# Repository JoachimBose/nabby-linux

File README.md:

# Nabby linux
This contains the buildroot, uboot & linux configurations for a hobby project. To get started, clone a new buildroot repository outside this one.
Then, from within the buildroot repository, execute:
```bash
BR2_EXTERNAL=../nabby-linux make nabby-linux_defconfig
```
This will import all the files from this repository. If you are new to buildroot, consider taking a look around this repository to see what you just imported.

after you compiled your buildroot, you should get a `flash.bin` image as described in the genimage.cfg. To flash it, put the chip in FEL-mode.
This is done by shorting chipselect of the spiflash to 3.3 volts and powering on the device, after powerup remove the short. Now you can use:
```bash
sunxi-fel -p spiflash-write 0 flash.bin
```
to flash the board while its in FEL mode.

# VUCTF-2026 board

The VUCTF26 board has support for the w5500 dev boards like the w850io or the cheaper USR-ES1. There exist also the Spookystats vulnerable website and the portalctl privilege escalation 
challenge which can be compiled as a buildroot package. Any questions are welcome towards joa0405 on discord!

## Acknowledgements
When we built the nabby board, we forked the repository from: [BasicCode](https://github.com/BasicCode/F1C100-Business-Card/tree/main/board/f1c100-business-card)
and we are very thankful for their contribution & GPL-2.0 license. In BasicCodes repository, they acknowledged help from the following authors:

This project is based heavily on the work of others; I would like to acknowledge these project in particular:
* https://github.com/thirtythreeforty/businesscard-linux/tree/master
* https://github.com/florpor/licheepi-nano/tree/master
* [F1C100 Datasheet](https://whycan.com/files/members/3/F1C100s_Datasheet_V1_0.pdf)
* [Lichee-Pi Nano](https://wiki.sipeed.com/hardware/en/lichee/Nano/Nano.html)

*

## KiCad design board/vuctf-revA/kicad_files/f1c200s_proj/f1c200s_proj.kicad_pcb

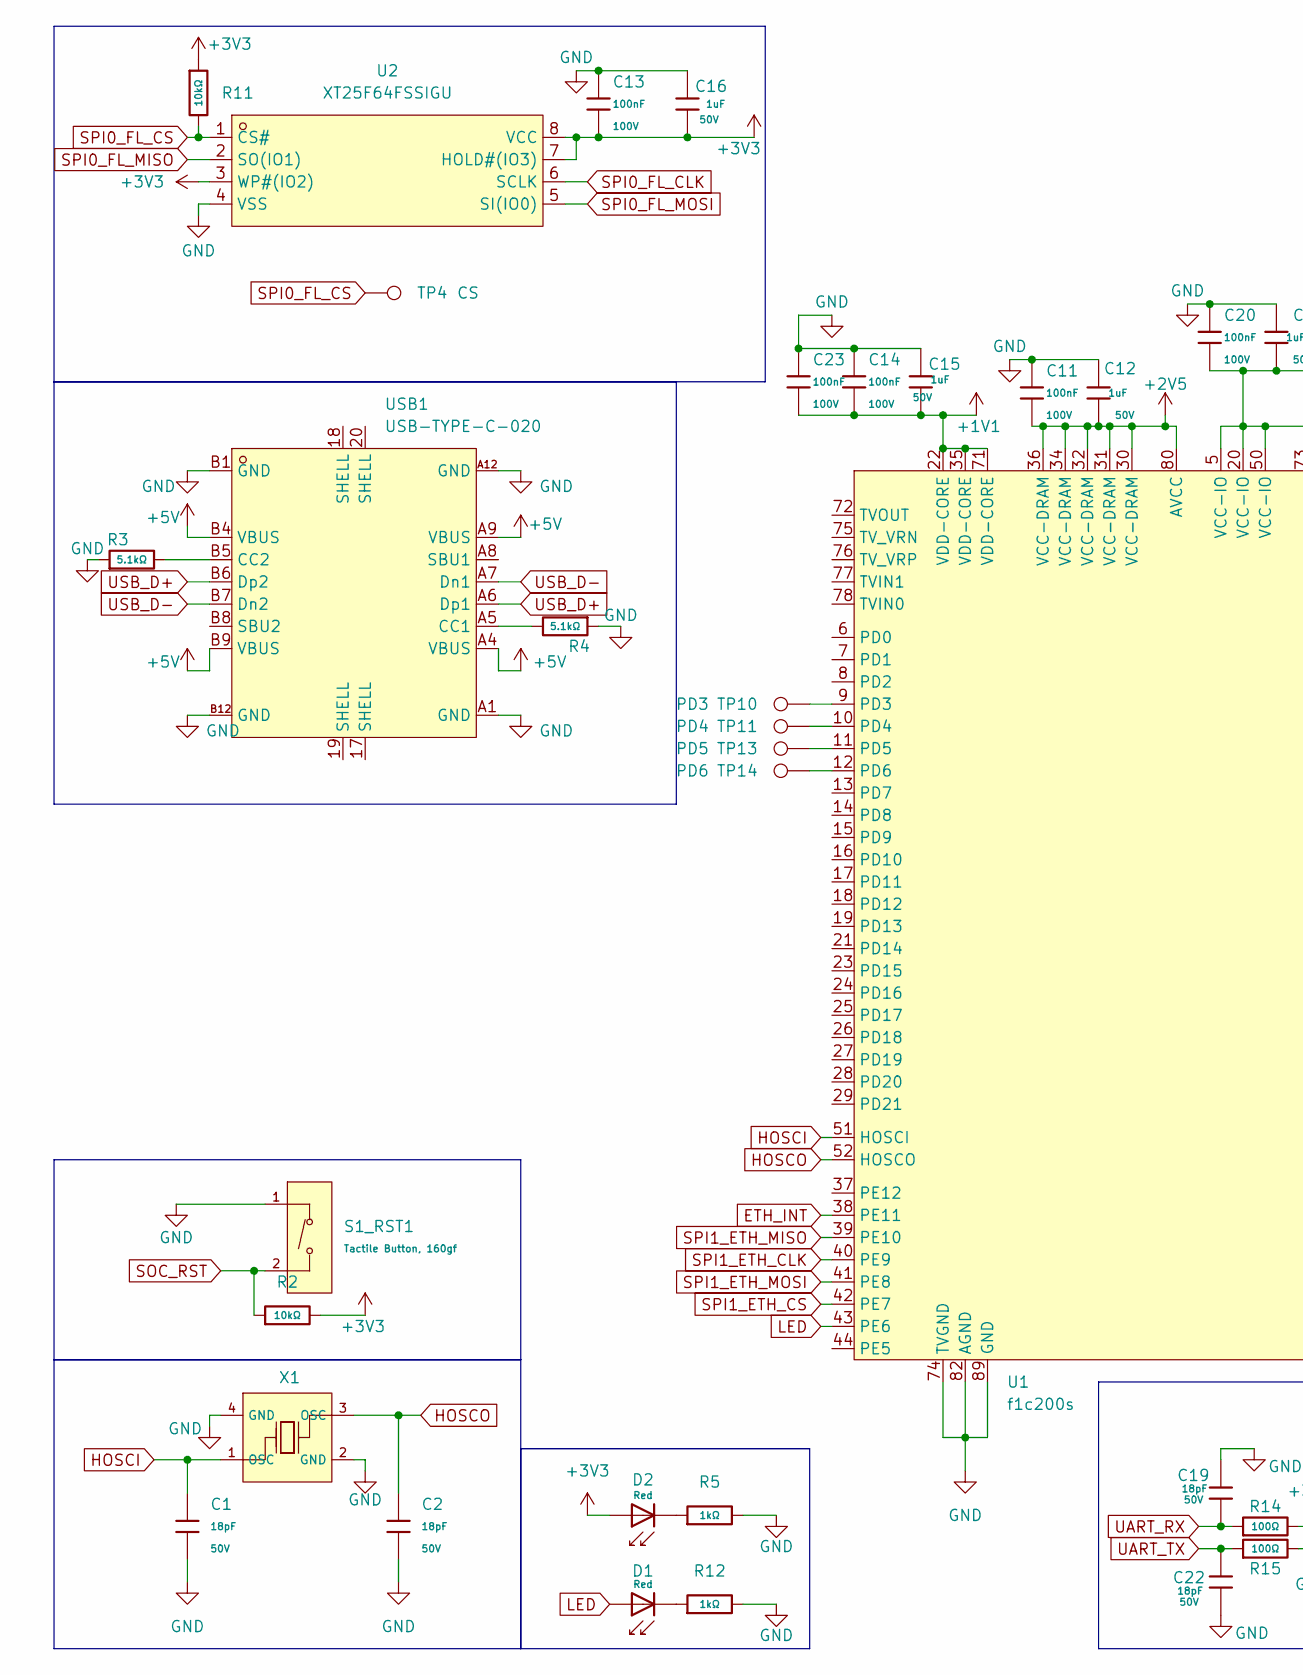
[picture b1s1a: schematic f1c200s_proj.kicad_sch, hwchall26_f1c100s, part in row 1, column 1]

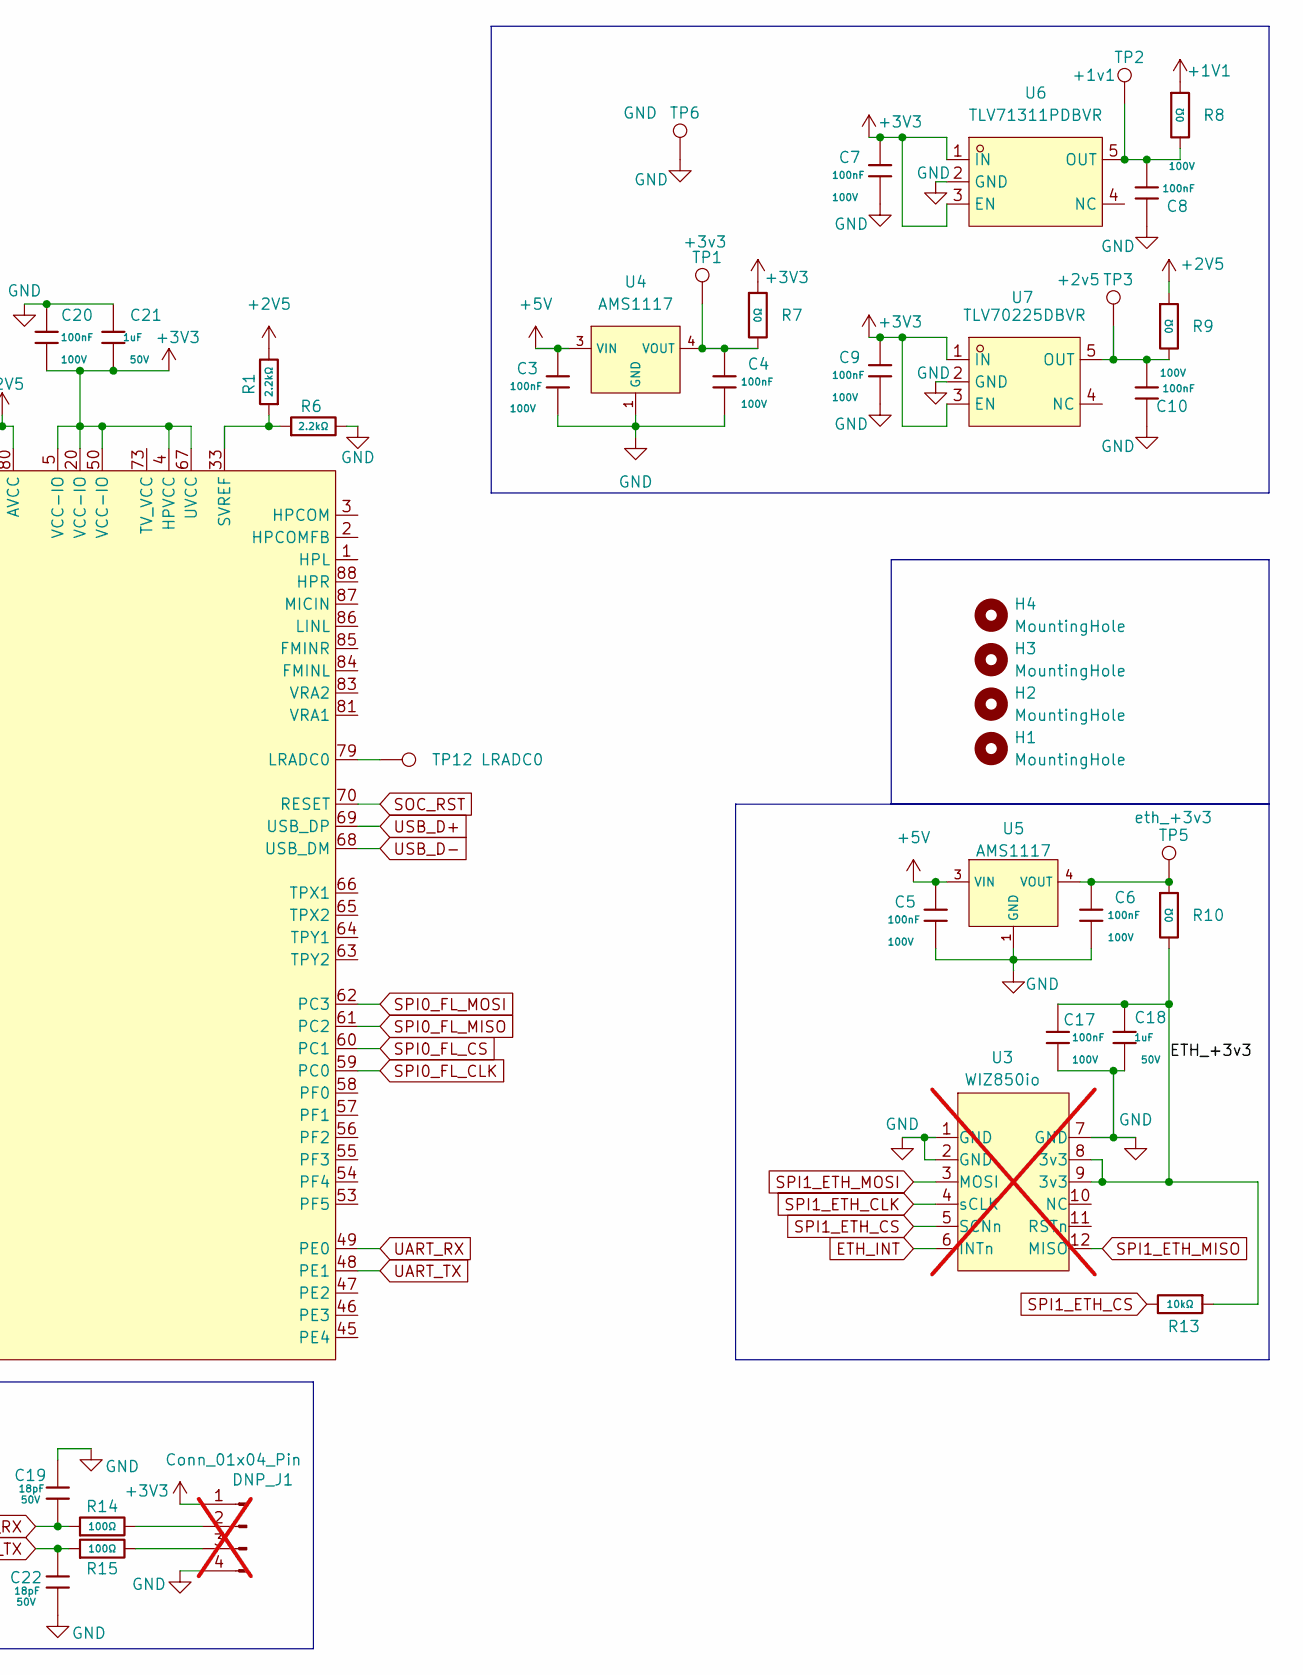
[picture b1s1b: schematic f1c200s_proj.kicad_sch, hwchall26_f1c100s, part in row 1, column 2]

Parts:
C1, C2, C19, C22: 18pF; C_0603; Voltage Rated 50V; Tolerance ±5%; Part CL10C180JB8NNNC; LCSC C1647
C3, C4, C5, C6, C7, C8, C9, C10, C11, C13, C14, C17, C20, C23: 100nF; C_0805; Voltage Rated 100V; Tolerance ±10%; Part CL21B104KCFNNNE; LCSC C28233
C12, C15, C16, C18, C21: 1uF; C_0805; Voltage Rated 50V; Tolerance ±10%; Part CL21B105KBFNNNE; LCSC C28323
D1, D2: Red; D_0603; Part KT-0603R; LCSC C2286
DNP_J1: Conn_01x04_Pin; PinHeader_1x04_P2.54mm_Vertical; not fitted
H1, H2, H3, H4: MountingHole; MountingHole_3.5mm
R1, R6: 2.2kΩ; R_0805; Overload Voltage (Max) 150V; Tolerance ±1%; Part 0805W8F2201T5E; LCSC C17520
R2, R11, R13: 10kΩ; R_0805; Overload Voltage (Max) 150V; Tolerance ±1%; Part 0805W8F1002T5E; LCSC C17414
R3, R4: 5.1kΩ; R_0805; Overload Voltage (Max) 150V; Tolerance ±1%; Part 0805W8F5101T5E; LCSC C27834
R5, R12: 1kΩ; R_0805; Overload Voltage (Max) 150V; Tolerance ±1%; Part 0805W8F1001T5E; LCSC C17513
R7, R8, R9, R10: 0Ω; R_0805; Overload Voltage (Max) 150V; Tolerance ±1%; Part 0805W8F0000T5E; LCSC C17477
R14, R15: 100Ω; R_0805; Overload Voltage (Max) 150V; Tolerance ±1%; Part 0805W8F1000T5E; LCSC C17408
S1_RST1: Tactile Button, 160gf; SW_TS-1088-AR02016; Voltage Rating (Dc) 12V; Part TS-1088-AR02016; LCSC C720477
TP1: +3v3; TestPoint_THTPad_2.0x2.0mm_Drill1.0mm
TP2: +1v1; TestPoint_THTPad_2.0x2.0mm_Drill1.0mm
TP3: +2v5; TestPoint_THTPad_2.0x2.0mm_Drill1.0mm
TP4: CS; TestPoint_THTPad_2.0x2.0mm_Drill1.0mm
TP5: eth_+3v3; TestPoint_THTPad_2.0x2.0mm_Drill1.0mm
TP6: GND; TestPoint_THTPad_2.0x2.0mm_Drill1.0mm
TP10: PD3; TestPoint_THTPad_2.0x2.0mm_Drill1.0mm
TP11: PD4; TestPoint_THTPad_2.0x2.0mm_Drill1.0mm
TP12: LRADC0; TestPoint_THTPad_2.0x2.0mm_Drill1.0mm
TP13: PD5; TestPoint_THTPad_2.0x2.0mm_Drill1.0mm
TP14: PD6; TestPoint_THTPad_2.0x2.0mm_Drill1.0mm
U1: f1c200s; QFN-88_L10.0-W10.0-P0.40-BL-EP6.75_f1c200s; Manufacturer Part F1C200S; LCSC Part Name Allwinner F1C200S
U2: XT25F64FSSIGU; FLASH-8pin; Manufacturer Part XT25F64FSSIGU; LCSC Part Name 3.3V 四路 IO 串行闪存
U3: WIZ850io; wiz850io-footprint; not fitted
U4, U5: AMS1117; SOT-223-3_L6.5-W3.4-P2.30-LS7.0-BR; Output Voltage 3.3V; Dropout Voltage 1.3V@(800mA); Part AMS1117-3.3; LCSC C6186
U6: TLV71311PDBVR; TI-LDO-1v1; Manufacturer Part TLV71311PDBVR; LCSC Part Name 1.1V 150mA 5.5V
U7: TLV70225DBVR; TI-LDO-2v5; Manufacturer Part TLV70225DBVR; LCSC Part Name 具有使能功能的 300mA、高 PSRR、低 IQ、低压降稳压器
USB1: USB-TYPE-C-020; USB-SMD_USB-TYPE-C-020; Manufacturer Part USB-TYPE-C-020; LCSC Part Name Type-C 母 卧贴
X1: X322524MOB4SI; OSC-SMD_4P-L3.2-W2.5-BL; Frequency Tolerance ±10ppm; Part X322525MOB4SI; LCSC C70590

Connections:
+1V1: C14.2, C15.2, C23.2, R8.1, U1.22 (VDD-CORE), U1.35 (VDD-CORE), U1.71 (VDD-CORE)
+2V5: C11.2, C12.2, R1.2, R9.1, U1.30 (VCC-DRAM), U1.31 (VCC-DRAM), U1.32 (VCC-DRAM), U1.34 (VCC-DRAM), U1.36 (VCC-DRAM), U1.80 (AVCC)
+3V3: C7.1, C9.1, C13.2, C16.2, C20.2, C21.2, D2.2, DNP_J1.1, R2.2, R7.1, R11.1, U1.4 (HPVCC), U1.5 (VCC-IO), U1.20 (VCC-IO), U1.50 (VCC-IO), U1.67 (UVCC), U2.3 (WP#(IO2)), U2.7 (HOLD#(IO3)), U2.8 (VCC), U6.1 (IN), U6.3 (EN), U7.1 (IN), U7.3 (EN)
+5V: C3.1, C5.1, U4.3 (VIN), U5.3 (VIN), USB1.A4 (VBUS), USB1.A9 (VBUS), USB1.B4 (VBUS), USB1.B9 (VBUS)
/ETH_+3v3: C17.1, C18.1, R10.2, R13.1, U3.8 (3v3), U3.9 (3v3)
ETH_INT: U1.38 (PE11), U3.6 (INTn)
GND: C1.2, C2.2, C3.2, C4.2, C5.2, C6.2, C7.2, C8.1, C9.2, C10.1, C11.1, C12.1, C13.1, C14.1, C15.1, C16.1, C17.2, C18.2, C19.1, C20.1, C21.1, C22.2, C23.1, DNP_J1.4, R3.1, R4.1, R5.2, R6.2, R12.2, S1_RST1.1 (A), TP6.1, U1.74 (TVGND), U1.82 (AGND), U1.89 (GND), U2.4 (VSS), U3.1 (GND), U3.2 (GND), U3.7 (GND), U4.1 (GND), U5.1 (GND), U6.2 (GND), U7.2 (GND), USB1.A1 (GND), USB1.A12 (GND), USB1.B1 (GND), USB1.B12 (GND), X1.2 (GND), X1.4 (GND)
HOSCI: C1.1, U1.51 (HOSCI), X1.1 (OSC)
HOSCO: C2.1, U1.52 (HOSCO), X1.3 (OSC)
LED: D1.2, U1.43 (PE6)
unnamed: C4.1, R7.2, TP1.1, U4.2 (VOUT), U4.4 (VOUT)
unnamed: C6.1, R10.1, TP5.1, U5.2 (VOUT), U5.4 (VOUT)
unnamed: D1.1, R12.1
unnamed: D2.1, R5.1
unnamed: DNP_J1.2, R14.2
unnamed: DNP_J1.3, R15.2
unnamed: TP12.1, U1.79 (LRADC0)
unnamed: TP10.1, U1.9 (PD3)
unnamed: TP11.1, U1.10 (PD4)
unnamed: TP13.1, U1.11 (PD5)
unnamed: TP14.1, U1.12 (PD6)
unnamed: R1.1, R6.1, U1.33 (SVREF)
unnamed: C8.2, R8.2, TP2.1, U6.5 (OUT)
unnamed: C10.2, R9.2, TP3.1, U7.5 (OUT)
unnamed: R4.2, USB1.A5 (CC1)
unnamed: R3.2, USB1.B5 (CC2)
SOC_RST: R2.1, S1_RST1.2 (B), U1.70 (RESET)
SPI0_FL_CLK: U1.59 (PC0), U2.6 (SCLK)
SPI0_FL_CS: R11.2, TP4.1, U1.60 (PC1), U2.1 (CS#)
SPI0_FL_MISO: U1.61 (PC2), U2.2 (SO(IO1))
SPI0_FL_MOSI: U1.62 (PC3), U2.5 (SI(IO0))
SPI1_ETH_CLK: U1.40 (PE9), U3.4 (sCLK)
SPI1_ETH_CS: R13.2, U1.42 (PE7), U3.5 (SCNn)
SPI1_ETH_MISO: U1.39 (PE10), U3.12 (MISO)
SPI1_ETH_MOSI: U1.41 (PE8), U3.3 (MOSI)
UART_RX: C19.2, R14.1, U1.49 (PE0)
UART_TX: C22.1, R15.1, U1.48 (PE1)
USB_D+: U1.69 (USB_DP), USB1.A6 (Dp1), USB1.B6 (Dp2)
USB_D-: U1.68 (USB_DM), USB1.A7 (Dn1), USB1.B7 (Dn2)

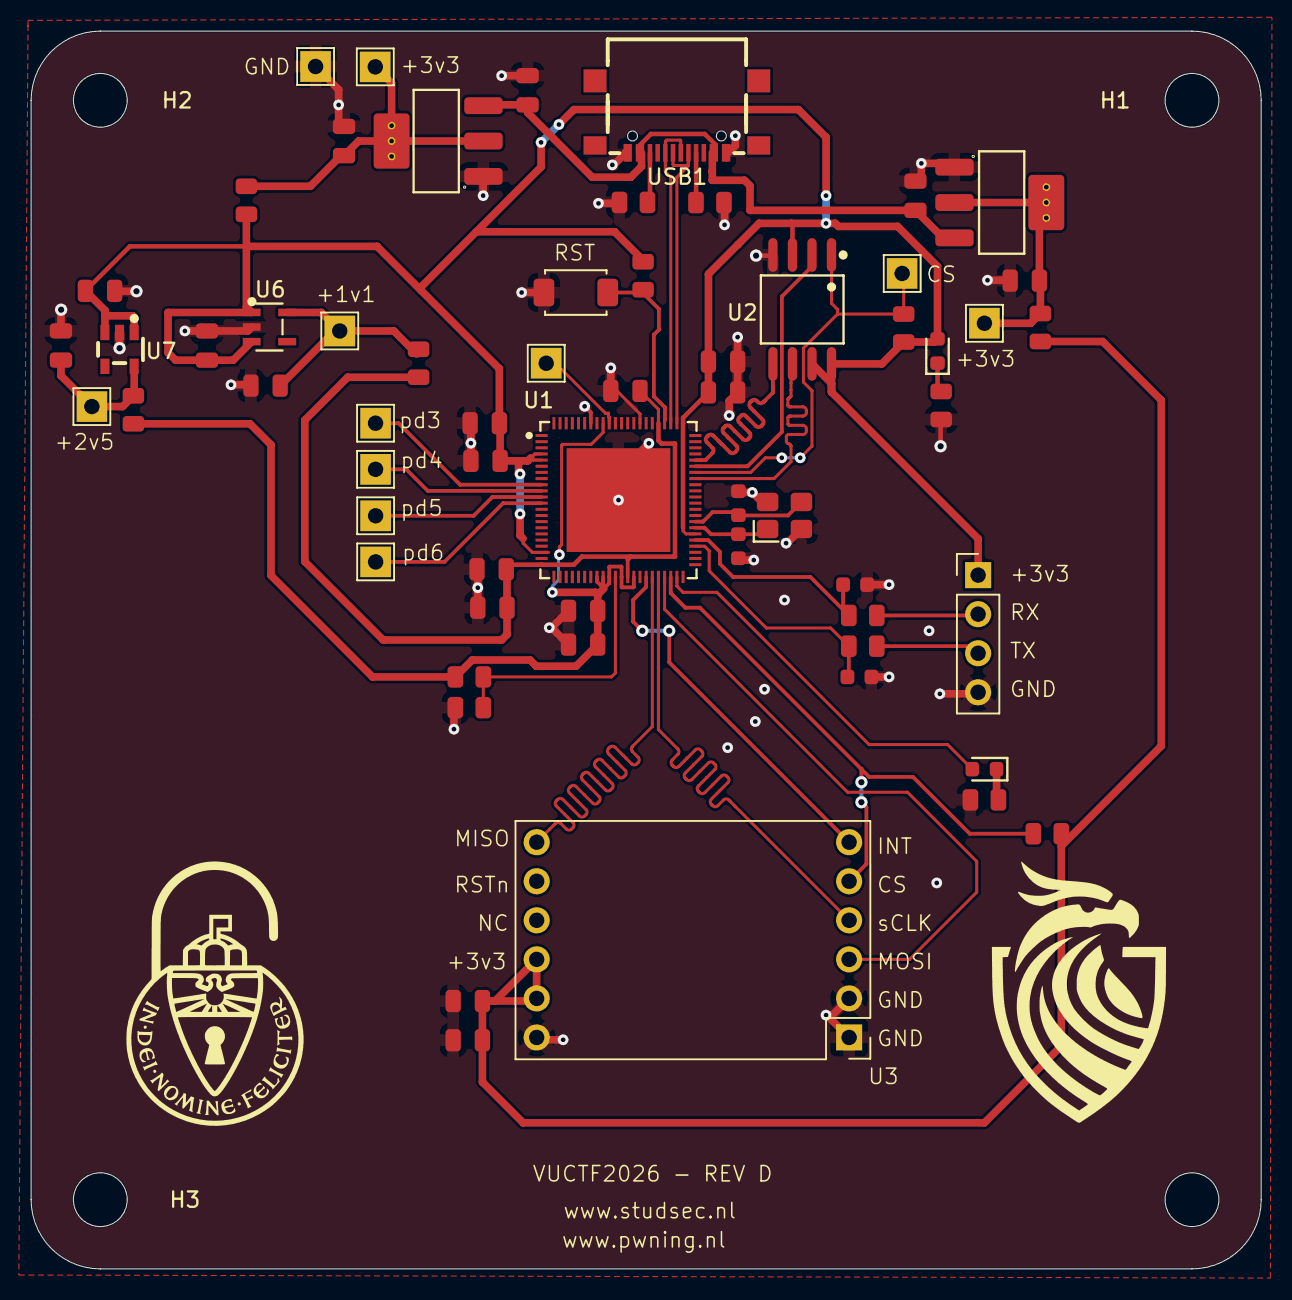
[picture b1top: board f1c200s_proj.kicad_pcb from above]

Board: 2 copper layers, 80.0 x 80.5 mm, 66 parts (0 on the bottom side), 39 nets.

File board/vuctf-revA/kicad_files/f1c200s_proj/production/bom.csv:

Designator,Footprint,Quantity,Value,LCSC Part #
"C1, C19, C2, C22",C_0603,4,18pF,C1647
"C10, C11, C13, C14, C17, C20, C23, C3, C4, C5, C6, C7, C8, C9",C_0805,14,100nF,C28233
"C12, C15, C16, C18, C21",C_0805,5,1uF,C28323
"D1, D2",D_0603,2,Red,C2286
"R1, R6",R_0805,2,2.2kΩ,C17520
"R10, R7, R8, R9",R_0805,4,0Ω,C17477
"R11, R13, R2",R_0805,3,10kΩ,C17414
"R12, R5",R_0805,2,1kΩ,C17513
"R14, R15",R_0805,2,100Ω,C17408
"R3, R4",R_0805,2,5.1kΩ,C27834
S1_RST1,SW_TS-1088-AR02016,1,"Tactile Button, 160gf",C720477
TP1,TestPoint_THTPad_2.0x2.0mm_Drill1.0mm,1,+3v3,
TP10,TestPoint_THTPad_2.0x2.0mm_Drill1.0mm,1,PD3,
TP11,TestPoint_THTPad_2.0x2.0mm_Drill1.0mm,1,PD4,
TP12,TestPoint_THTPad_2.0x2.0mm_Drill1.0mm,1,LRADC0,
TP13,TestPoint_THTPad_2.0x2.0mm_Drill1.0mm,1,PD5,
TP14,TestPoint_THTPad_2.0x2.0mm_Drill1.0mm,1,PD6,
TP2,TestPoint_THTPad_2.0x2.0mm_Drill1.0mm,1,+1v1,
TP3,TestPoint_THTPad_2.0x2.0mm_Drill1.0mm,1,+2v5,
TP4,TestPoint_THTPad_2.0x2.0mm_Drill1.0mm,1,CS,
TP5,TestPoint_THTPad_2.0x2.0mm_Drill1.0mm,1,eth_+3v3,
TP6,TestPoint_THTPad_2.0x2.0mm_Drill1.0mm,1,GND,
U1,QFN-88_L10.0-W10.0-P0.40-BL-EP6.75_f1c200s,1,f1c200s,C2879851
U2,FLASH-8pin,1,~,
"U4, U5",SOT-223-3_L6.5-W3.4-P2.30-LS7.0-BR,2,AMS1117,C6186
U6,TI-LDO-1v1,1,TLV71311PDBVR,C205964
U7,TI-LDO-2v5,1,TLV70225DBVR,C2877849
USB1,USB-SMD_USB-TYPE-C-020,1,USB-TYPE-C-020,
X1,OSC-SMD_4P-L3.2-W2.5-BL,1,X322524MOB4SI,C70590

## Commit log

2026-02-15 Forked: nabby linux board booting
2026-02-15 renamed files
2026-02-16 Added new lctech-pi-f1c200s
2026-02-16 genimage.cfg for the sd card
2026-02-18 sd-card creation
2026-02-18 lctech-pi: progress on sdcard
    Linux boots, but immediately panics. I understand now how the partition table works. I also understand how u-boot boots
2026-02-18 linux booting
2026-02-19 Fix: remove old demos
2026-02-19 Added: fork for f1c200s ethernet
2026-02-20 More work: uart problems
2026-02-21 Fix: boot console now moved to uart2 due to pins clashing with spi
2026-02-24 fix: banner
2026-02-24 Attach w5500
2026-02-24 fix: dts syntax error
2026-02-24 added ethernet
2026-03-02 continue network configuration
2026-03-02 dhcp online
2026-03-17 fix: no host genimage
2026-03-18 Made: Copied lctech-pi-ether to template vuctf-revA
2026-03-19 Fix: dts should be ready for linux
2026-03-22 Added super simple package
2026-03-22 fix: wrong filesystem format
2026-03-22 fix: wrong prefix
2026-03-23 Add: website now serving on x86
2026-03-25 made: site fully operational and exploited
2026-03-25 fix: update spookystats port
2026-03-25 Made: package template portalctl
2026-03-26 fix: prepared for boot
2026-03-27 fix: uboot is booting from ram
2026-03-28 fix: flash detected
2026-03-30 Fix: net-working
2026-03-30 fix: shared lib not installed
2026-03-30 fix: add nc
2026-03-31 added scripts for compile and testprogram for DIO testing
2026-04-02 made portalctl, and made it vulnerable
2026-04-03 Fix: tried to make it more exploitable
2026-04-03 fix: attempt 2 to make it more exploitable
2026-04-04 fix: attempt 5 to make it more exploitable
2026-04-04 fix: attempt 6 to make more exploitable
2026-04-04 fix: attempt 7 to make it more exploitable
2026-04-04 fix: attempt 8 to make it more exploitable
2026-04-04 attempt 9 at making it more exploitable
2026-04-04 added svc
2026-04-04 fix: attempt 10 to make it more exploitable
2026-04-04 attempt 11 at making it more exploitable
2026-04-05 fix: crash
2026-04-05 configure uboot without console
2026-04-05 fix: removed c++ dependency from spookystats
2026-04-05 Fix: uboot now restricts cli
2026-04-06 Fix: prepared for vuctf
2026-04-06 final attempt at making it more exploitable
2026-04-06 fix: spookystats compilation
2026-04-09 fix: get ready for vuctf 2
2026-04-09 web challenge auth layer added
2026-04-09 DTS setup correctly for ILI9341TFT with /dev/fb0
2026-04-10 fix: portalctl more exploitable
2026-04-14 Add GNU General Public License version 2
2026-04-14 final changes on the hardware
2026-04-14 image.rgb and console display correctly
2026-05-11 Added files
2026-05-11 Fix: image does not render properly
2026-05-26 added: kicad project
2026-06-18 Fix formatting in README.md acknowledgments section
2026-06-18 Fix formatting in API version print statement
